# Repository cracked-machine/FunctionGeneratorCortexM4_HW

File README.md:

## Cortex M4-based Function Generator (Hardware)
A function generator powered by STM32 G4.

Required Kicad Hardware library: https://github.com/cracked-machine/KicadLibrary

For details of the MCU configuration and firmware refer to [FunctionGeneratorCortexM4_SW](https://github.com/cracked-machine/FunctionGeneratorCortexM4_SW)

Note, RevB was the final design. RevC was not built and is an untested future proposal. 

### System Overview

Input signals can be used as a trigger, capturing on voltage level or edge detection.

DAC1 synthesises the main output signal waveform and sends it to a voltage gain amplifier ([LTC6910-3](https://www.analog.com/media/en/technical-documentation/data-sheets/6910fb.pdf)). The signal is then mixed with the DC offset signal from DAC2. The signal is then passes through a lowpass filter to remove any high frequency noise.

DAC2 is a DC signal 0-3.3V. This is sent to a buffer and inverting buffer. Either output is selected using the MCU-controlled SPDT switch IC ([TS12A12511DCNR](http://www.ti.com/lit/ds/symlink/ts12a12511.pdf)). This applies a software configurable DC offset between +3.3V and -3.3V to the main output signal.

DAC3 is an output signal synchronised to DAC1 to be used for triggering purposes.

### Daughter boards ###

The display, controls and i/o connectors are connected via daughter boards to the main board via ribbon cable. An example of the display daughter board and its ribbon cable can be seen in the video below:

https://www.instagram.com/p/CA5NSdBhmBY/?utm_source=ig_web_copy_link

### Power supply

##### Current Consumption:

|Component|Type|Current|
|---------|----|-------|
|STM32G4|MCU|42mA (max)|
|TL972|OPAMP|3.2mA (per amplifier)|
|LTC6910-3|PGA|4.9mA|
|TS12A12511|SPDT|1uA|
|74LVC1G3157|SPDT|35uA|
|LCD TFT|display|60mA|
|*__Total__*||*__120mA__*|

The 9V input is regulated down to 3.3V and 5V for the MCU and LCD display.

Dual supply for the VGA and opamps are provided using multiple [TPS60400](http://www.ti.com/lit/ds/symlink/tps60402.pdf) charge pumps. TPS60400 are rated at 60mA output but in testing was found to be less. Therefore, multiple TPS60400 were required to provide "point-of-load" regulation.

Additional filtering is provided at the MCU supply pins with L1 and L2 ferrite beads and C1-C12 bypass capacitors.

A midpoint reference 2.5V voltage is provided to the LTC6910-3 VGA using a  [TL431DBZ](https://www.ti.com/lit/ds/symlink/tl431.pdf) precision programmable reference.

### Limitations

The power supply limits the output to 9Vp-p. The output swing of the VGA limits this further.

The VGA output current is limited to ~25mA. This is also limited by the power supply.

Due to the settling time of the VGA, smooth sweeps between output amplitude levels using this IC was not possible. As such, the output is fixed to the maximum VGA level. Output amplitude control was handled by the firmware instead.

See [LTC6910-3](https://www.analog.com/media/en/technical-documentation/data-sheets/6910fb.pdf) datasheet for more information.

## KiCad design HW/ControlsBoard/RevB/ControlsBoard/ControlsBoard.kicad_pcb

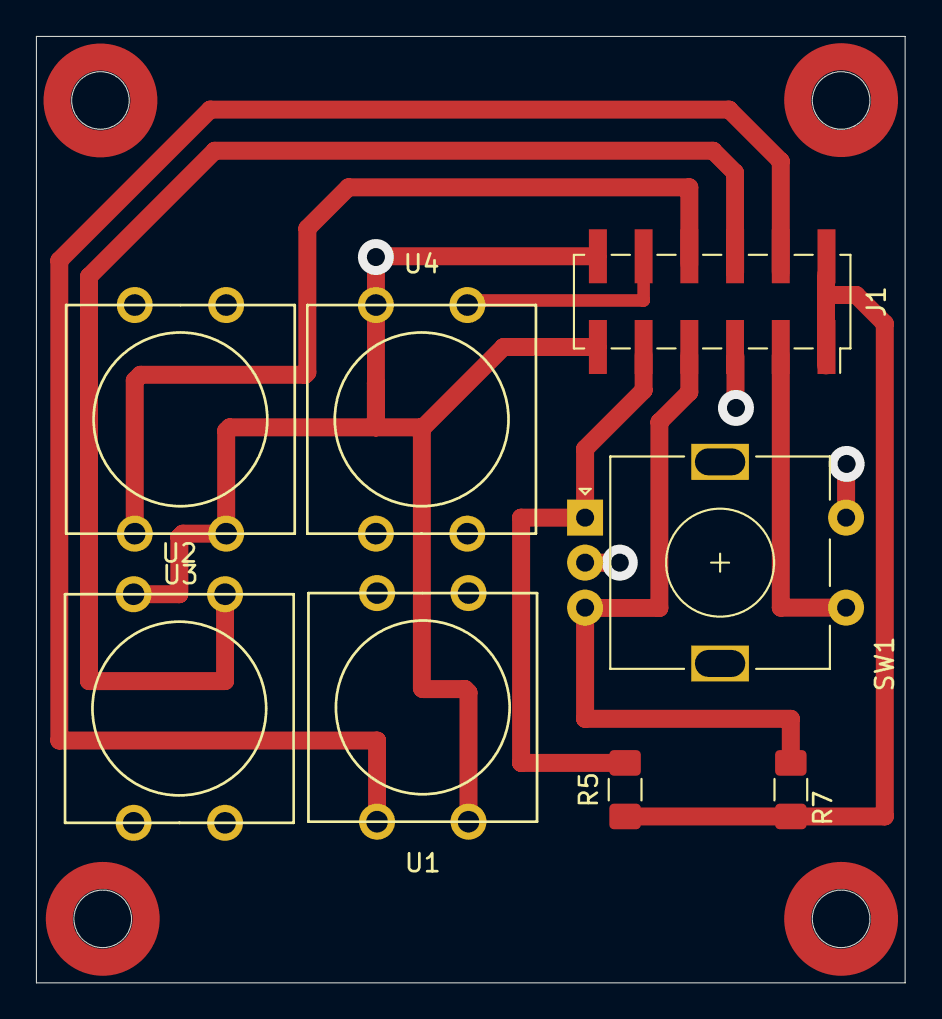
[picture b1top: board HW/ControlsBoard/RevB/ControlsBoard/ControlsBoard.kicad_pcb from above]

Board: 2 copper layers, 48.3 x 52.6 mm, 8 parts (0 on the bottom side), 9 nets.

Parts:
J1: Conn_02x06_Odd_Even; PinSocket_2x06_P2.54mm_Vertical_SMD
R5, R7: 10K; R_1206_3216Metric_Pad1.42x1.75mm_HandSolder
SW1: Rotary_Encoder_Switch; RotaryEncoder_Alps_EC11E-Switch_Vertical_H20mm
U1, U2, U3, U4: Tactile_Switch_SPST-NO; 12x12x7_3mmTactilePushButtonMomentary

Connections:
+3V3: J1.1, J1.2, R5.1, R7.1
/Controls/BTN1: J1.4, U1.4
/Controls/BTN2: J1.6, U2.4
/Controls/BTN3: J1.8, U3.4
/Controls/BTN4: J1.10, U4.4
/Controls/ENC_A: J1.9, R5.2, SW1.A
/Controls/ENC_B: J1.7, R7.2, SW1.B
/Controls/ENC_SW: J1.3, SW1.S1
GNDS: J1.5, J1.11, J1.12, SW1.C, SW1.S2, U1.2, U2.2, U3.2, U4.2

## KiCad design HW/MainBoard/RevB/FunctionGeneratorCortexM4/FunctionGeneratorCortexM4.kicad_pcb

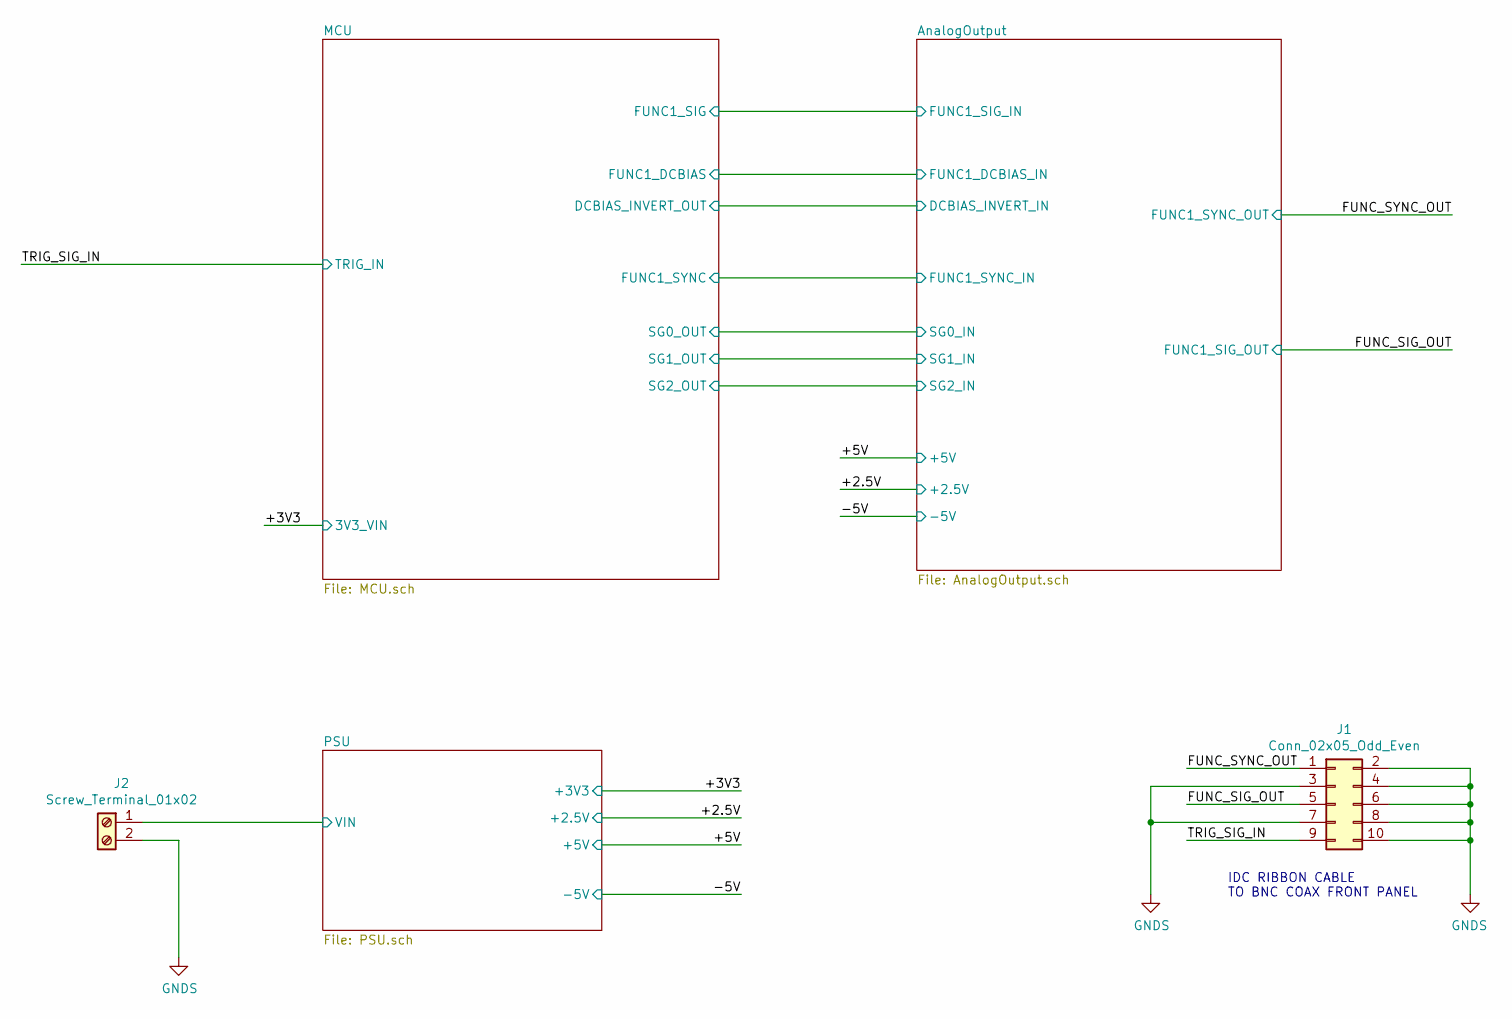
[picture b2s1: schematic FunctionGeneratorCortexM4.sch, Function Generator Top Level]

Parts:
J1: Conn_02x05_Odd_Even; IDC-Header_2x05_P2.54mm_Vertical
J2: Screw_Terminal_01x02; TerminalBlock_bornier-2_P5.08mm

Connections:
/FUNC_SIG_OUT: J1.5; also elsewhere on the board
/FUNC_SYNC_OUT: J1.1; also elsewhere on the board
/PSU/VIN: J2.1; also elsewhere on the board
/TRIG_SIG_IN: J1.9; also elsewhere on the board

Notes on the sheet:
IDC RIBBON CABLE TO BNC COAX FRONT PANEL

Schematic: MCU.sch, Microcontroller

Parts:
J3: Conn_02x06_Odd_Even; IDC-Header_2x06_P2.54mm_Vertical
J4: Conn_01x06; PinHeader_1x06_P2.54mm_Vertical
J5: Conn_01x03; PinHeader_1x03_P2.54mm_Vertical
J6: Conn_02x04_Odd_Even; IDC-Header_2x04_P2.54mm_Vertical
J7: Conn_02x07_Odd_Even; PinHeader_2x07_P1.27mm_Vertical_SMD
JP10: Jumper_NC_Small; PinHeader_1x02_P2.54mm_Vertical
R7: 10K; R_1206_3216Metric_Pad1.42x1.75mm_HandSolder
R11: 100R; R_1206_3216Metric_Pad1.42x1.75mm_HandSolder
TP14, TP15: TestPoint; TestPoint_Pad_1.0x1.0mm
U2: SN74LVC1G3157DCKR; SOT-363_SC-70-6_Handsoldering
U6: STM32G474RET; LQFP-64_10x10mm_P0.5mm

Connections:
/+3V3: J3.1, J3.2, J4.1, J6.1, J6.8, J7.3, U2.8; also elsewhere on the board
/AnalogOutput/DCBIAS_INVERT_IN: U6.17 (PA3); also elsewhere on the board
/AnalogOutput/SG0_IN: U6.24 (PB0); also elsewhere on the board
/AnalogOutput/SG1_IN: U6.23 (PC5); also elsewhere on the board
/AnalogOutput/SG2_IN: U6.22 (PC4); also elsewhere on the board
/MCU/ADC_IN3: TP14.1, U2.3, U6.14 (PA2)
/MCU/BTN1: J3.4, U6.3 (PC14-OSC32_IN)
/MCU/BTN2: J3.6, U6.4 (PC15-OSVC32_OUT)
/MCU/BTN3: J3.8, U6.5 (PF0-OSC_IN)
/MCU/BTN4: J3.10, U6.6 (PF1-OSC_OUT)
/MCU/COMP1_INP: TP15.1, U2.2, U6.13 (PA1)
/MCU/ENC_A: J3.9, U6.8 (PC0)
/MCU/ENC_B: J3.7, U6.9 (PC1)
/MCU/ENC_SW: J3.3, U6.10 (PC2)
/MCU/FUNC1_DCBIAS: U6.19 (PA5); also elsewhere on the board
/MCU/FUNC1_SIG: U6.18 (PA4); also elsewhere on the board
/MCU/FUNC1_SYNC: U6.20 (PA6); also elsewhere on the board
/MCU/TFT_CS: J6.3, U6.60 (PB7)
/MCU/TFT_DC: J6.5, U6.59 (PB6)
/MCU/TFT_MOSI: J6.6, U6.54 (PC12)
/MCU/TFT_RST: J6.4, U6.62 (PB9)
/MCU/TFT_SCK: J6.7, U6.52 (PC10)
/MCU/TIM2_TF1FP1: U2.1, U6.12 (PA0)
/MCU/TRIGMUX1: U2.6, U6.40 (PC8)
/MCU/TRIGMUX2: U2.5, U6.41 (PC9)
/MCU/T_NRST: J4.5, J7.12, U6.7 (PG10-NRST)
/MCU/T_SWCLK: J4.2, J7.6, U6.50 (PA14)
/MCU/T_SWDIO: J4.4, J7.4, U6.49 (PA13)
/MCU/T_SWO: J4.6, J7.8, U6.56 (PB3)
/TRIG_SIG_IN: U2.7; also elsewhere on the board
unnamed: J7.11, R11.1
unnamed: JP10.1, R7.2
unnamed: JP10.2, U6.61 (PB8-BOOT0)

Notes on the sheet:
TIM1_CH1
TIM1_CH2
Using Internal VREF
Control Front Panel Connector RotEncoder and Tactile SPST
MIPI10/STDC14 ICP Connector
6-pin SWD ICP Connector
TFT Front Panel Display Connector
GPIO_EXTI2
GPIO_EXTI14
GPIO_EXTI15
GPIO_EXTI0
GPIO_EXTI1
SPI3
GPIO_OUTPUT

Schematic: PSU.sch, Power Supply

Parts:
C1, C5, C6, C7, C8, C12, C13, C25, C31: 100nF; C_1206_3216Metric_Pad1.42x1.75mm_HandSolder
C2, C4, C10, C11, C30: 1uF; C_1206_3216Metric_Pad1.42x1.75mm_HandSolder
C3: 4.7uF; C_1206_3216Metric_Pad1.42x1.75mm_HandSolder
C14, C27, C28, C29: 10Uf; C_1206_3216Metric_Pad1.42x1.75mm_HandSolder
C32: 10uF; C_1206_3216Metric_Pad1.42x1.75mm_HandSolder
D1: 10V; D_SOD-123F
D2, D3, D4: LED; LED_1206_3216Metric_Pad1.42x1.75mm_HandSolder
JP3: Jumper_NC_Small; SolderJumper-2_P1.3mm_Bridged_Pad1.0x1.5mm
L1, L2: 600R@100MHz; L_1206_3216Metric_Pad1.42x1.75mm_HandSolder
Q1: DMG2301L; SOT-23
R5, R6, R20: 4K7; R_1206_3216Metric_Pad1.42x1.75mm_HandSolder
R8: 100K; R_1206_3216Metric_Pad1.42x1.75mm_HandSolder
R12: 10K; R_1206_3216Metric_Pad1.42x1.75mm_HandSolder
R13: 6K2; R_1206_3216Metric_Pad1.42x1.75mm_HandSolder
R22: 1K; R_1206_3216Metric_Pad1.42x1.75mm_HandSolder
TP1, TP2, TP3, TP4, TP12, TP16: TestPoint; TestPoint_Pad_1.0x1.0mm
U1: NCP51460SN33T1G; SOT-23
U3: LP3992-33B5F; TSOT-23-5
U4, U5: NCP1729; SOT-23-6_Handsoldering
U6: STM32G474RET; LQFP-64_10x10mm_P0.5mm
U8: LM1117-5.0; SOT-223-3_TabPin2
U10: TL431DBZ; SOT-23

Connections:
/+2.5V: R12.1, R22.1, TP16.1, U10.1 (K); also elsewhere on the board
/+3V3: C2.1, C3.1, C5.1, C6.1, C7.1, C8.1, C10.1, L2.1, R20.1, TP4.1, U3.5 (VOUT), U6.1 (VBAT), U6.16 (VDD), U6.32 (VDD), U6.48 (VDD), U6.64 (VDD); also elsewhere on the board
/PSU/3V3REF: C1.1, L1.1, TP3.1, U1.2 (VO)
/PSU/VIN: Q1.3 (D); also elsewhere on the board
unnamed: C11.2, C12.2, L1.2, U6.28 (VREF+)
unnamed: C14.1, U4.3
unnamed: C14.2, U4.5
unnamed: C27.1, U5.3
unnamed: C27.2, U5.5
unnamed: C30.1, U3.4 (BYP)
unnamed: C31.1, D1.1 (K), Q1.2 (S), U8.3 (VI)
unnamed: D1.2 (A), Q1.1 (G), R8.1
unnamed: D2.2 (A), R5.2
unnamed: D3.1 (K), R6.2
unnamed: D4.2 (A), R20.2
unnamed: JP3.2, U3.3 (INH)
unnamed: L2.2, U6.29 (VDDA)
unnamed 74: R12.2, R13.1, U10.2 (REF); also elsewhere on the board

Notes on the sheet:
Max Vin: 28V
PGA NEGATIVE SUPPLY
DC BIAS NEGATIVE SUPPLY
MICRO CONTROLLER POWER
Max Vin: 5V
Not required if using LP3992
Closed for LP3992 Open if not required
Current Consumption: STM32G4 (MCU) 42mA (max) TL972 (OPAMP) 3.2mA (per amplifier) LTC6910 (PGA) 4.9mA TS12A12511 (SPDT) 1uA 74LVC1G3157 (SPDT) 35uA TFT display 60mA
Max 5.5V
Max Vin: 15V

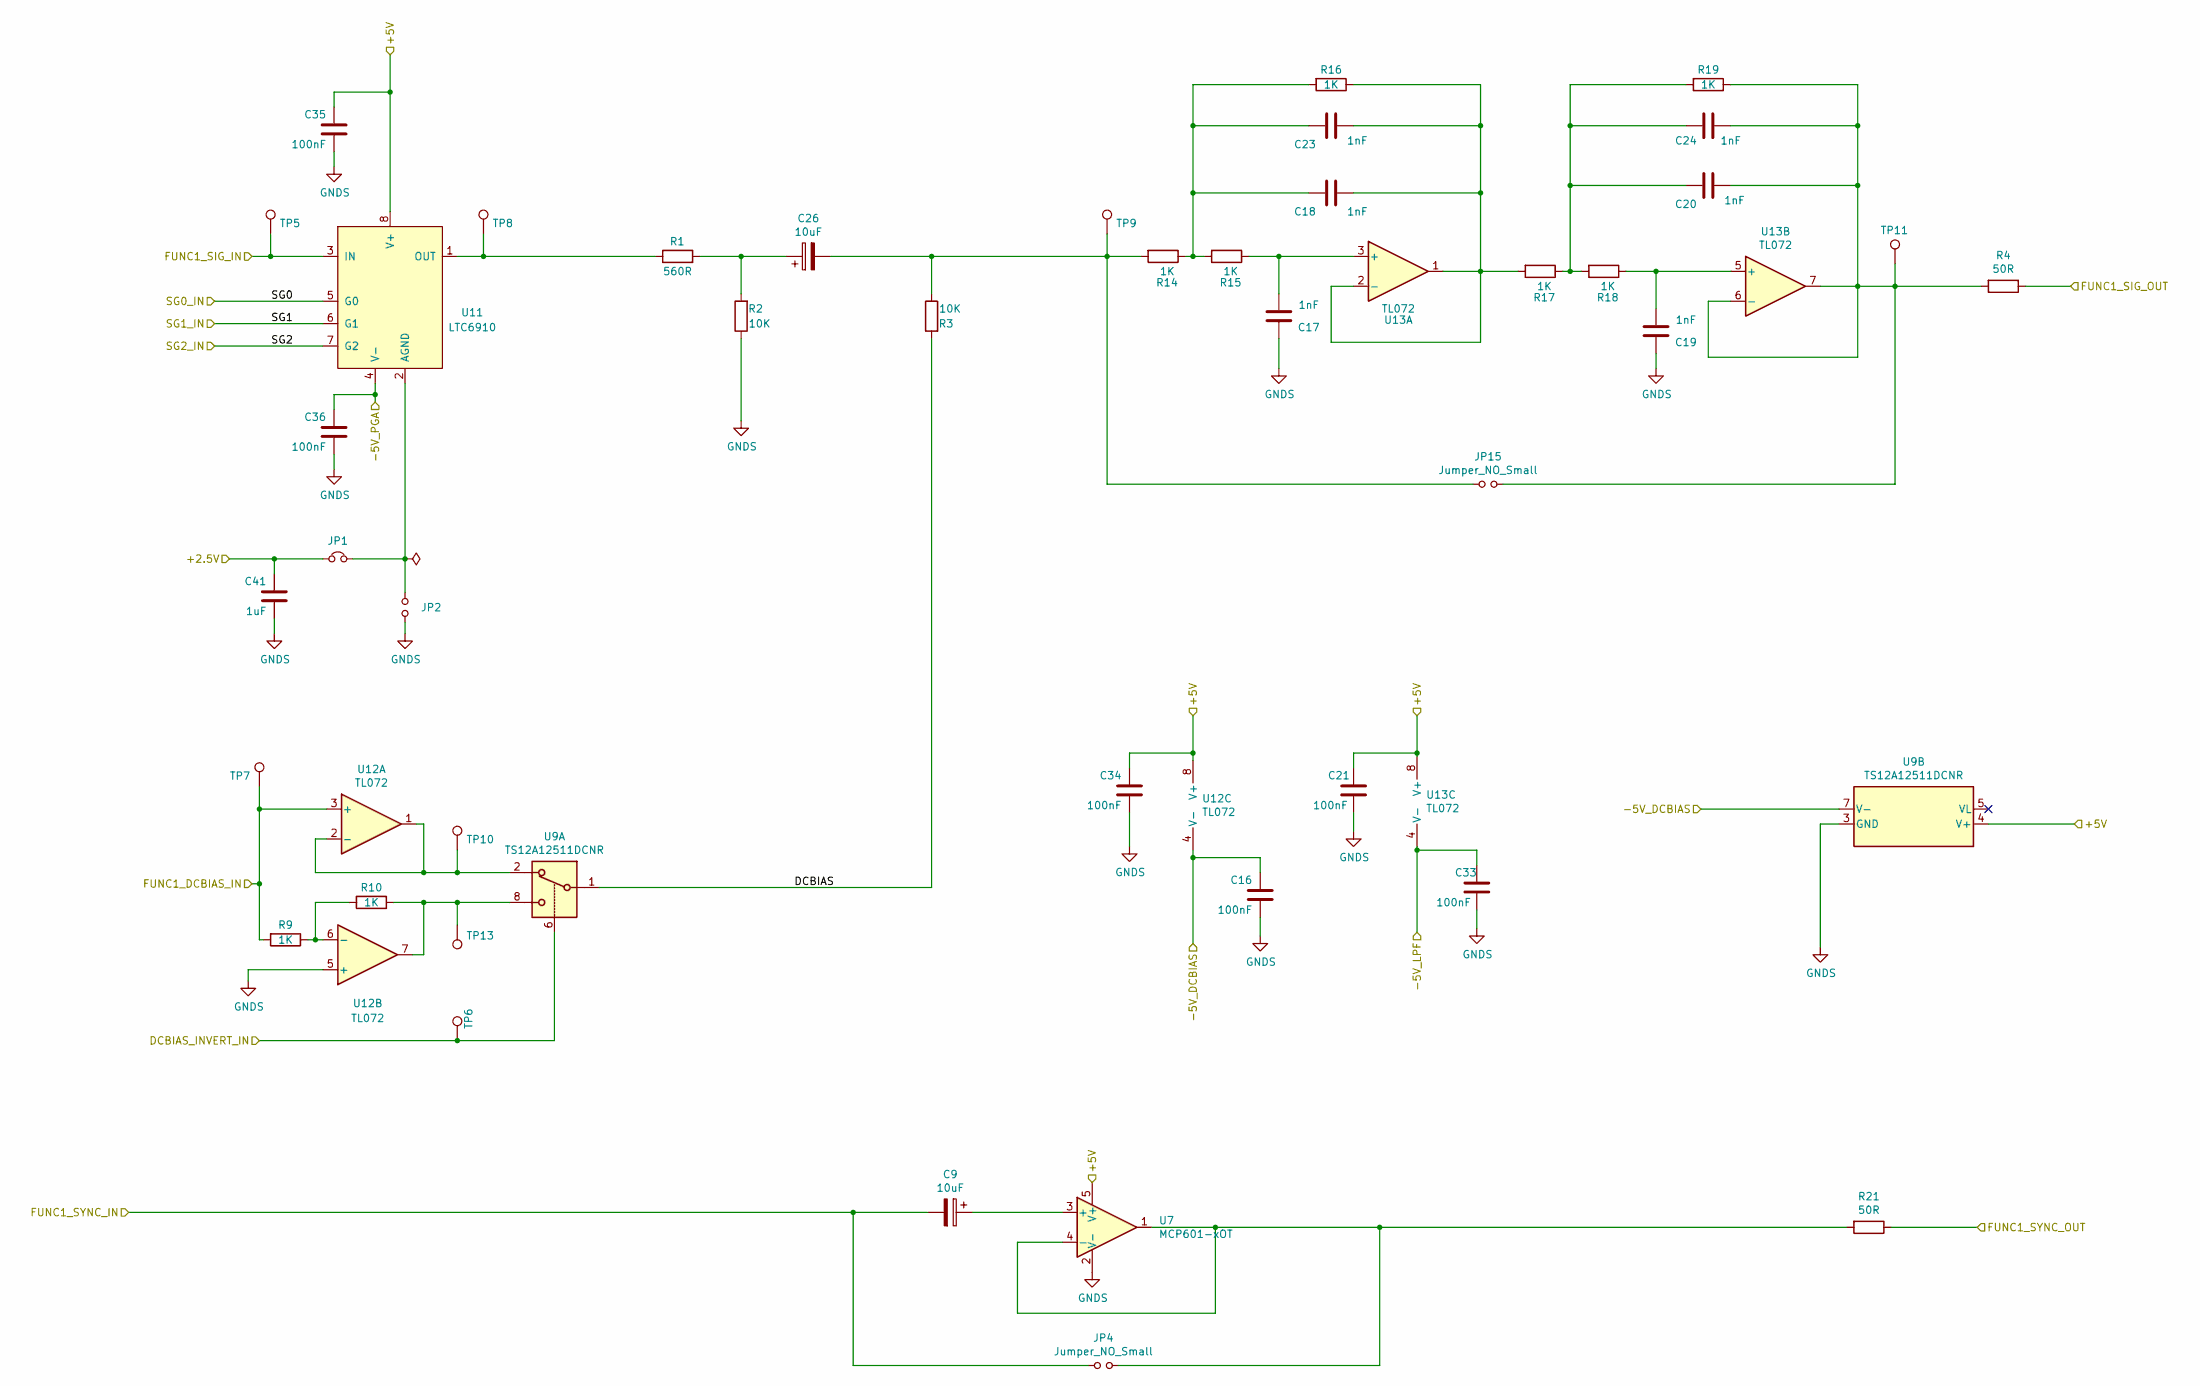
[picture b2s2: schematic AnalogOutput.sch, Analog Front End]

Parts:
C9, C26: 10uF; CP_Elec_4x5.7
C16, C21, C33, C34, C35, C36: 100nF; C_1206_3216Metric_Pad1.42x1.75mm_HandSolder
C17, C18, C19, C20, C23, C24: 1nF; C_1206_3216Metric_Pad1.42x1.75mm_HandSolder
C41: 1uF; C_1206_3216Metric_Pad1.42x1.75mm_HandSolder
JP1: Jumper_NC_Small; SolderJumper-2_P1.3mm_Bridged_Pad1.0x1.5mm
JP2, JP4, JP15: Jumper_NO_Small; SolderJumper-2_P1.3mm_Open_Pad1.0x1.5mm
R1: 560R; R_1206_3216Metric_Pad1.42x1.75mm_HandSolder
R2, R3: 10K; R_1206_3216Metric_Pad1.42x1.75mm_HandSolder
R4, R21: 50R; R_1206_3216Metric_Pad1.42x1.75mm_HandSolder
R9, R10, R14, R15, R16, R17, R18, R19: 1K; R_1206_3216Metric_Pad1.42x1.75mm_HandSolder
TP5, TP6, TP7, TP8, TP9, TP10, TP11, TP13: TestPoint; TestPoint_Pad_1.0x1.0mm
U7: MCP601-xOT; SOT-23-5
U9: TS12A12511DCNR; SOT-23-8_Handsoldering
U11: LTC6910; TSOT-23-8
U12, U13: TL072; SOIC-8_3.9x4.9mm_P1.27mm

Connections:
/+2.5V: C41.2, JP1.1; also elsewhere on the board
/AnalogOutput/DCBIAS: R3.2, U9.1
/AnalogOutput/DCBIAS_INVERT_IN: TP6.1, U9.6; also elsewhere on the board
/AnalogOutput/SG0_IN: U11.5 (G0); also elsewhere on the board
/AnalogOutput/SG1_IN: U11.6 (G1); also elsewhere on the board
/AnalogOutput/SG2_IN: U11.7 (G2); also elsewhere on the board
/FUNC_SIG_OUT: R4.1; also elsewhere on the board
/FUNC_SYNC_OUT: R21.1; also elsewhere on the board
/MCU/FUNC1_DCBIAS: R9.2, TP7.1, U12.3 (+); also elsewhere on the board
/MCU/FUNC1_SIG: TP5.1, U11.3 (IN); also elsewhere on the board
/MCU/FUNC1_SYNC: C9.2, JP4.1; also elsewhere on the board
unnamed: C9.1, U7.3 (+)
unnamed: C17.2, R15.1, U13.3 (+)
unnamed: C18.1, C23.1, R16.1, R17.2, U13.1, U13.2 (-)
unnamed: C18.2, C23.2, R14.1, R15.2, R16.2
unnamed: C19.2, R18.1, U13.5 (+)
unnamed: C20.1, C24.1, JP15.2, R4.2, R19.1, TP11.1, U13.6 (-), U13.7
unnamed: C20.2, C24.2, R17.1, R18.2, R19.2
unnamed: C26.1, R1.2, R2.2
unnamed: C26.2, JP15.1, R3.1, R14.2, TP9.1
unnamed: JP1.2, JP2.1, U11.2 (AGND)
unnamed: JP4.2, R21.2, U7.1, U7.4 (-)
unnamed: R1.1, TP8.1, U11.1 (OUT)
unnamed: R10.1, TP13.1, U9.8, U12.7
unnamed: R9.1, R10.2, U12.6 (-)
unnamed: TP10.1, U9.2, U12.1, U12.2 (-)

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
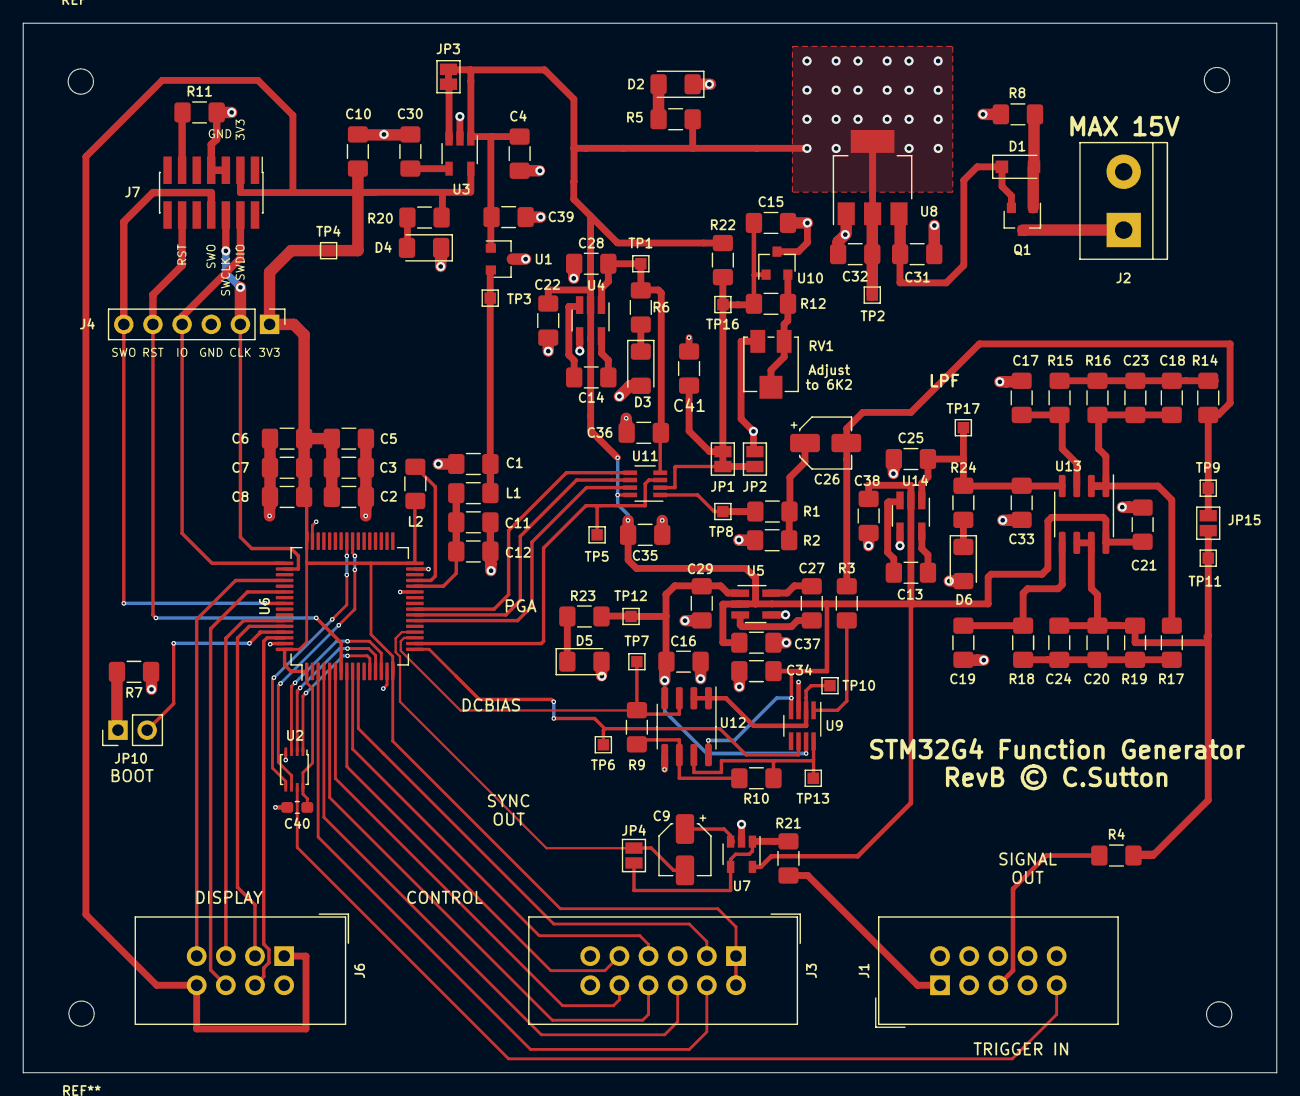
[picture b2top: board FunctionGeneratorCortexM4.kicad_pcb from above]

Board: 2 copper layers, 109.2 x 91.4 mm, 115 parts (0 on the bottom side), 77 nets.

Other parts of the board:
C15: 1nF; C_1206_3216Metric_Pad1.42x1.75mm_HandSolder
C22, C37, C38, C39: 100nF; C_1206_3216Metric_Pad1.42x1.75mm_HandSolder
C40: 100nF; C_0603_1608Metric_Pad1.05x0.95mm_HandSolder
D5, D6: LED; LED_1206_3216Metric_Pad1.42x1.75mm_HandSolder
R23, R24: 4K7; R_1206_3216Metric_Pad1.42x1.75mm_HandSolder
RV1: R_POT_TRIM; Potentiometer_Bourns_3314J_Vertical
TP17: TestPoint; TestPoint_Pad_1.0x1.0mm
U14: TPS60400; SOT-23-5_HandSoldering

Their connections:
/+2.5V: C15.1; also elsewhere on the board
/+3V3: C40.1; also elsewhere on the board
unnamed: D5.1, R23.2
unnamed: D6.1, R24.2
unnamed 74: RV1.1, RV1.2; also elsewhere on the board

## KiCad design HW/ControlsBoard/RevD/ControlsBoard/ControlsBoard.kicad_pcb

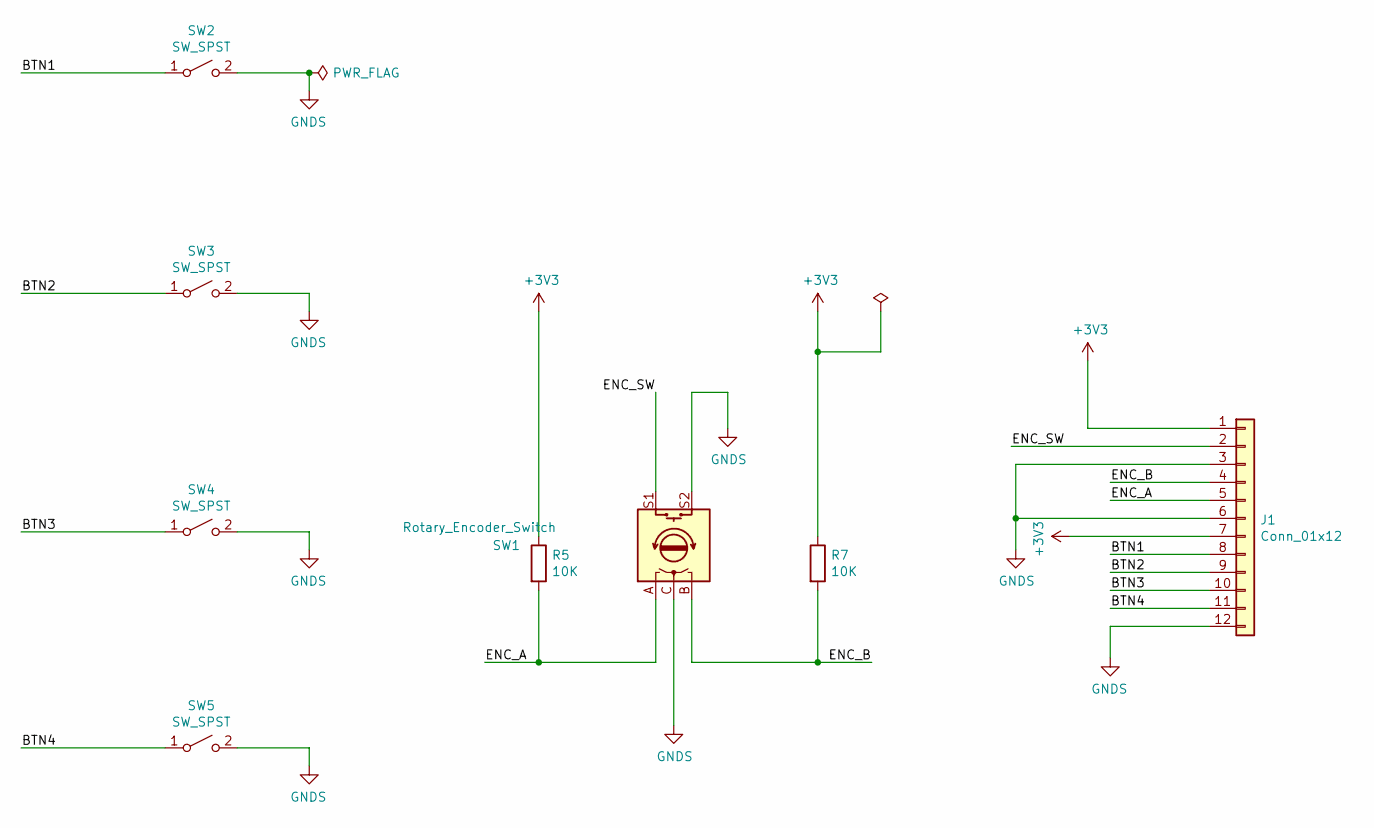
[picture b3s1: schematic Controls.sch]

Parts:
J1: Conn_01x12; Molex_Pico-Clasp_501331-1207_1x12-1MP_P1.00mm_Vertical
R5, R7: 10K; R_1206_3216Metric_Pad1.42x1.75mm_HandSolder
SW1: Rotary_Encoder_Switch; RotaryEncoder_Alps_EC11E-Switch_Vertical_H20mm
SW2, SW3, SW4, SW5: SW_SPST; SW_PUSH_6mm

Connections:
+3V3: J1.1, J1.7, R5.1, R7.1
/Controls/BTN1: J1.8, SW2.1 (A)
/Controls/BTN2: J1.9, SW3.1 (A)
/Controls/BTN3: J1.10, SW4.1 (A)
/Controls/BTN4: J1.11, SW5.1 (A)
/Controls/ENC_A: J1.5, R5.2, SW1.A
/Controls/ENC_B: J1.4, R7.2, SW1.B
/Controls/ENC_SW: J1.2, SW1.S1
GNDS: J1.3, J1.6, J1.12, SW1.C, SW1.S2, SW2.2 (B), SW3.2 (B), SW4.2 (B), SW5.2 (B)

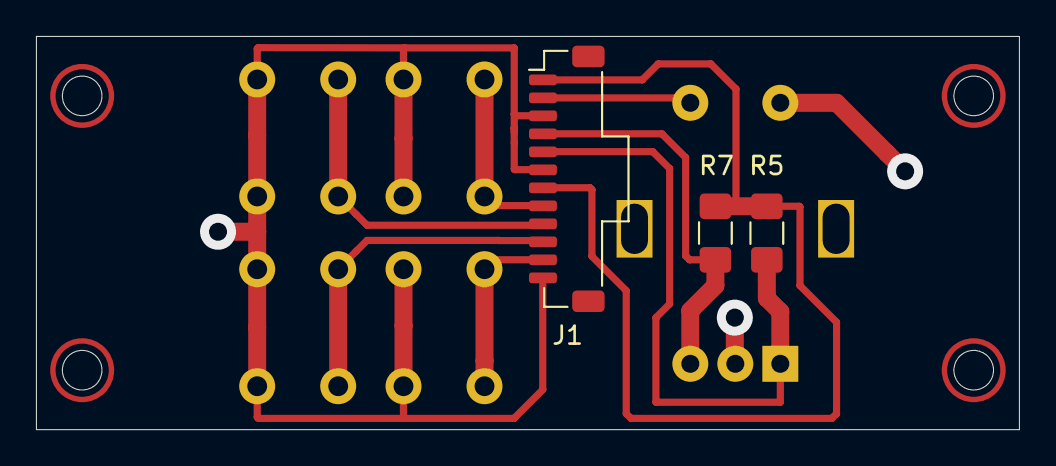
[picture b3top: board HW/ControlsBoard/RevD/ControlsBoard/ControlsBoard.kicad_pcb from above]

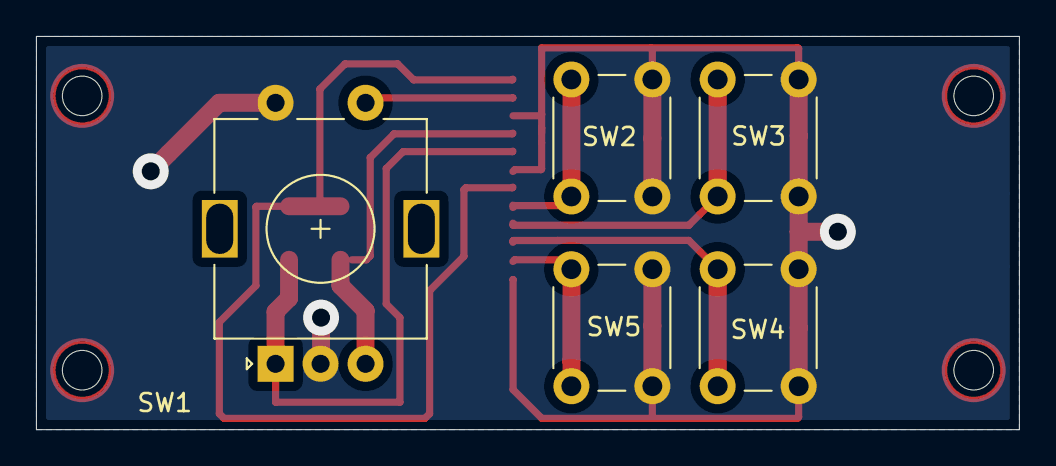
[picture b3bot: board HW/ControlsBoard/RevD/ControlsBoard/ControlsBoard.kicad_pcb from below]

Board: 2 copper layers, 54.6 x 21.8 mm, 8 parts (5 on the bottom side), 9 nets.

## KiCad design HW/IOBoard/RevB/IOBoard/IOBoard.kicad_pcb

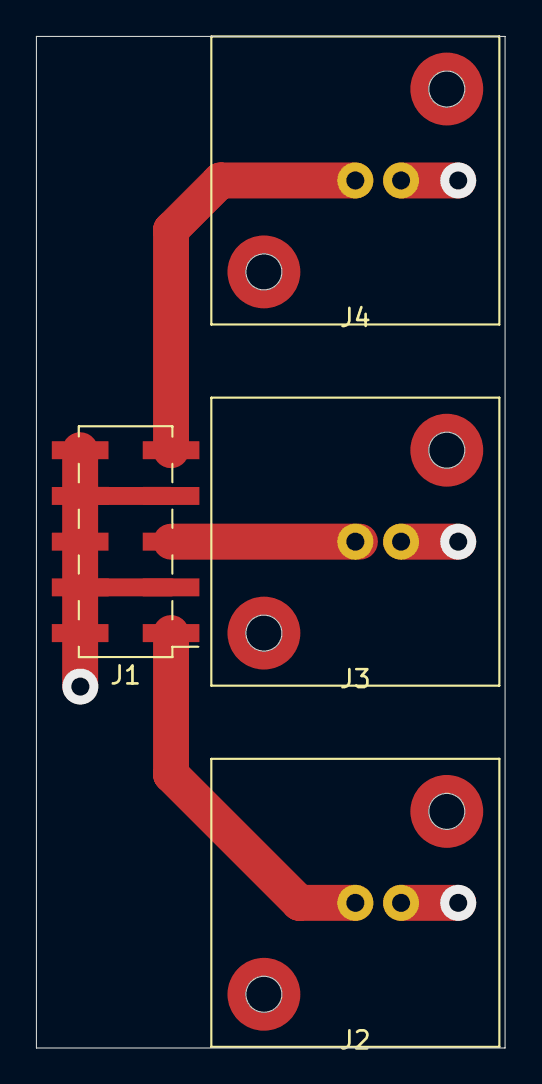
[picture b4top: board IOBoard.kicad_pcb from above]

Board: 2 copper layers, 26.0 x 56.2 mm, 4 parts (0 on the bottom side), 4 nets.

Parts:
J1: Conn_02x05_Odd_Even; PinHeader_2x05_P2.54mm_Vertical_SMD
J2, J3, J4: Conn_Coaxial; RSProStraight50OhmPCBMountBulkheadFittingBNC_5260279

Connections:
/FUNC_SIG_OUT: J1.5, J3.1
/FUNC_SYNC_OUT: J1.1, J2.1
/TRIG_SIG_IN: J1.9, J4.1
GNDS: J1.2, J1.3, J1.4, J1.6, J1.7, J1.8, J1.10, J2.2, J3.2, J4.2

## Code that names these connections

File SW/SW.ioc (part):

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Mcu.Name=STM32G474R(B-C-E)Tx
Mcu.Package=LQFP64
Mcu.UserName=STM32G474RETx
PA0.Signal=S_TIM2_CH1
PA1.Mode=INP
PA1.Signal=COMP1_INP
PA13.Mode=Trace_Asynchronous_SW
PA13.Signal=SYS_JTMS-SWDIO
PA14.Mode=Trace_Asynchronous_SW
PA14.Signal=SYS_JTCK-SWCLK
PA2.Mode=IN3-Single-Ended
PA2.Signal=ADC1_IN3
PA3.GPIOParameters=GPIO_Label
PA3.GPIO_Label=DCBIAS_INVERT
PA3.Signal=GPIO_Output
PA4.Signal=COMP_DAC11_group
PA5.Signal=COMP_DAC12_group
PA6.Signal=COMP_DAC21_group
PB0.GPIOParameters=GPIO_Label
PB0.GPIO_Label=SG0e
PB0.Signal=GPIO_Output
PB3.Mode=Trace_Asynchronous_SW
PB3.Signal=SYS_JTDO-SWO
PB6.GPIOParameters=GPIO_Label
PB6.GPIO_Label=DC
PB6.Signal=GPIO_Output
PB7.GPIOParameters=GPIO_Label
PB7.GPIO_Label=CS
PB7.Signal=GPIO_Output
PB9.GPIOParameters=GPIO_Label
PB9.GPIO_Label=RST
PB9.Signal=GPIO_Output
PC0.Signal=S_TIM1_CH1
PC1.Signal=S_TIM1_CH2
PC10.Mode=Full_Duplex_Master
PC10.Signal=SPI3_SCK
PC11.Mode=Full_Duplex_Master
PC11.Signal=SPI3_MISO
PC12.Mode=Full_Duplex_Master
PC12.Signal=SPI3_MOSI
PC14-OSC32_IN.GPIOParameters=GPIO_Label
PC14-OSC32_IN.GPIO_Label=GPIO_EXTI14_BTN1
PC14-OSC32_IN.Signal=GPXTI14
PC15-OSC32_OUT.GPIOParameters=GPIO_Label
PC15-OSC32_OUT.GPIO_Label=GPIO_EXTI15_BTN2
PC15-OSC32_OUT.Signal=GPXTI15
PC2.GPIOParameters=GPIO_Label
PC2.GPIO_Label=GPIO_EXTI2_ENC_SW
PC2.Signal=GPXTI2
PC3.GPIOParameters=GPIO_Label
PC3.GPIO_Label=GPIO_CH1_MUX
PC3.Signal=GPIO_Output
PC4.GPIOParameters=GPIO_Label
PC4.GPIO_Label=SG2
PC4.Signal=GPIO_Output
PC5.GPIOParameters=GPIO_Label
PC5.GPIO_Label=SG1
PC5.Signal=GPIO_Output
PF0-OSC_IN.GPIOParameters=GPIO_Label
PF0-OSC_IN.GPIO_Label=GPIO_EXTI0_BTN3
PF0-OSC_IN.Signal=GPXTI0
PF1-OSC_OUT.GPIOParameters=GPIO_Label
PF1-OSC_OUT.GPIO_Label=GPIO_EXTI1_BTN4
PF1-OSC_OUT.Signal=GPXTI1
RCC.HSE_VALUE=8000000
RCC.SYSCLKFreq_VALUE=16000000
board=custom

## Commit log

2020-03-02 HW UPDATE
    - Added PSU block
    - Added MCU block
2020-03-03 hw update
    - Added MCU section
2020-03-03 libs updated
2020-03-03 Finished Schema
2020-03-03 hw update
    Added bypass jumper for output filter
2020-03-03 hw update
    added passives to dc bias stage
2020-03-03 Completed RevA layout
2020-03-04 Finished RevA Layout
    Dummy STMCubeMX project included in SW dir
2020-03-04 updated RevA
    Generated GERBERS
2020-03-04 readme update
2020-03-04 uploaded diagram
    FunctionGeneratorM4_TopLevel.png
2020-03-04 updated readme
    added vector gfx diagrams: svg
2020-03-04 added stylesheet for readme
2020-03-04 moved style.css
2020-03-04 updated style.css
2020-03-04 Added diagram
    FunctionGeneratorM4_AnalogFrontEnd.svg
2020-03-04 Added Schema PDF
    Added to RevA.md
2020-03-04 Added schema svg
    Added to reva.md
2020-03-13 Added front panel boards
2020-03-13 Started HW RevB
2020-03-14 REVB Update
    - Changed TRIGIN J5 header to 2.54mm
    - Changed IO J1 header to 2x05
    - Added second charge pump IC
    - Changed analog output circuit
2020-03-14 Replaced LDO
    changed SOT223 (MCP1703) to SO23-5 (LP3992)
2020-03-14 Modified PowerSupply section
    - Added +2.5V ref
    - Added Vin->5V LDO
2020-03-14 save update
2020-03-15 REVB DRAFT LAYOUT
2020-03-15 OPTIMIZED REVB LAYOUT
2020-03-15 Regenerated schema diagrams
2020-03-15 Final RevB Layout completed
2020-03-31 updated front panel board layouts
2020-04-06 Added Revb designs for I/O and control panels
2020-04-06 updated control panel
2020-04-12 Created FrontPanel drawing
2020-05-18 Added RevC Control Panel
    Uses 55mm x 20mm PCB outline
    Uses 6mm switches rather than 12mm
2020-05-26 Created RevC - MainBoard and ControlBoard
2020-05-28 Created RevD using PicoClasp p1.0 connector
2020-05-29 Updated MainBoard RevC
    - Block diagram and connections completed on schematic
    - Need to check MCU pin availability
2020-05-29 Changed OFFSET SPDT to DG470
2020-05-29 Added two-series resistors in PGA feedback
2020-05-29 Created RevE ControlBoard to use 2.54 SMD header
    Header is at the top of the board to let buttons and encoder be closer together
2020-05-30 updated front panel svg
2020-05-30 Created Front Panel board layout
2020-06-01 Created FrontPanel layout
2020-06-01 updated frontpanel layout
2020-06-03 update analog input schema
2020-06-08 Added OutputAmplifier stage board
2020-09-13 updated readme
    - Added system overview with functional block diagram
    - Added limitation overview
2020-09-13 updated readme
    -- Added power supply section
2021-05-26 Added 3D models for front cover
2021-06-18 Create LICENSE

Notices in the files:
HW/MainBoard/RevB/FunctionGeneratorCortexM4/FunctionGeneratorCortexM4.kicad_pcb:
RevB © C.Sutton
